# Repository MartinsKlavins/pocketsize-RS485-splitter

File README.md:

# Pocketsize RS485 splitter
Pocketsize RS485 splitter for DMX512 signal. Created for everyday use with focus on problematic device isolation, connection for far separated devices, simple "Y" type splitting.

### Technical info
* It is active, have seperate power supply for each DMX output and input.
* Galvanic and optic isolation for each DMX output and input.
* MAX485, 6N137 and 74HC14 for signal pathway.

### Notes
* AC/DC and DC/DC converters are main advantage of this splitter. Power supply is created with 4 converters. First stage – 230V AC to 12V DC, second stage – multiple 12/05V DC/DC. There are variety of them, but I don’t suggest to use 05/05 (because they didn’t gave steady 5V output, atleast not for me). Didn’t helped capacitors and LDO (for example L4941BV) for stabilization. Any way, the are small-sized and great solution!

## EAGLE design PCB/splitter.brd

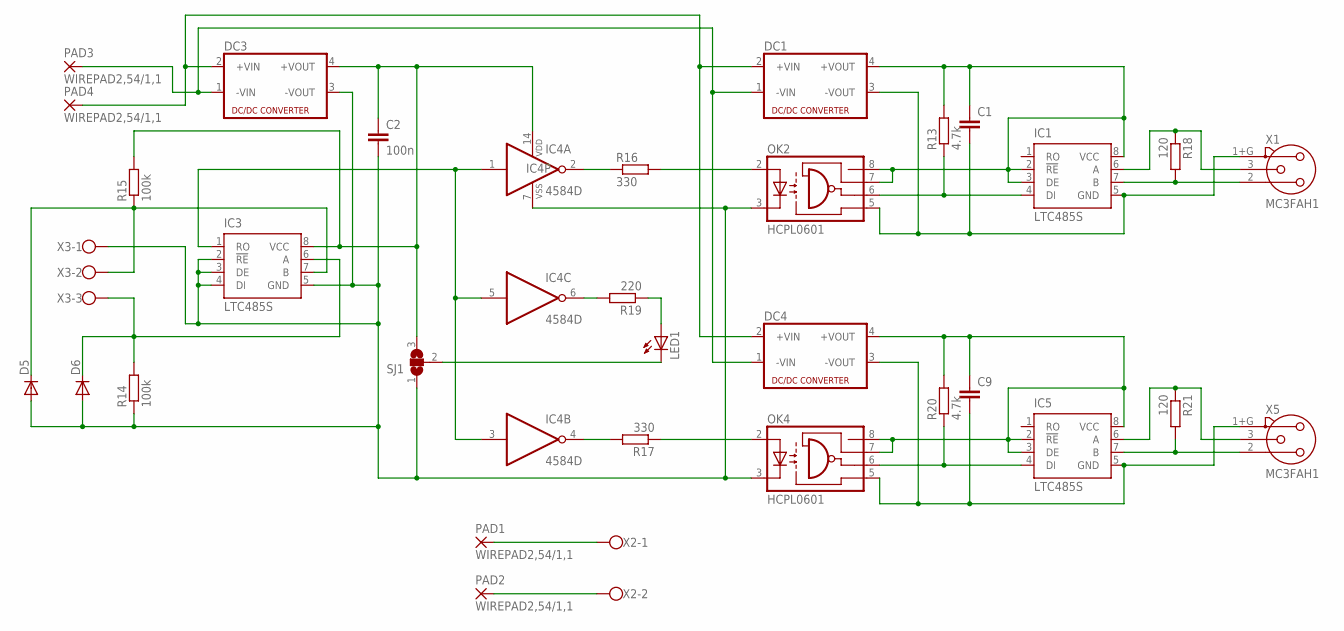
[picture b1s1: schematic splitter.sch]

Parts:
C1, C9: C-EUC1206K; C1206K
C2: 100n; C1206K
D5, D6: DIODE-SOD80C; SOD80C
DC1, DC3, DC4: NME
IC1, IC3, IC5: LTC485S; SOIC8
IC4: 4584D; SO14
LED1: LED_E; LED_1206
OK2, OK4: HCPL0601; SOIC08
PAD1, PAD2, PAD3, PAD4: WIREPAD2,54/1,1; 2,54/1,1
R13, R20: 4.7k; M1206
R14, R15: 100k; M1206
R16, R17: 330; M1206
R18, R21: 120; M1206
R19: 220; M1206
SJ1: SJ2W; SJ_2
X1, X5: MC3FAH1; NC3FAH1
X2: W237-102
X3: W237-103

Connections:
unnamed: LED1.C, SJ1.2
unnamed: IC1.6 (A), R18.1, X1.3
unnamed: IC5.7 (B), R21.2, X5.2
unnamed: IC1.4 (DI), OK2.6 (VO), R13.1
unnamed: C1.1, DC1.4 (+VOUT), IC1.2 (!RE), IC1.3 (DE), IC1.8 (VCC), OK2.7 (VE), OK2.8 (VCC), R13.2
unnamed: IC5.6 (A), R21.1, X5.3
unnamed: IC5.4 (DI), OK4.6 (VO), R20.1
unnamed: C9.2, DC4.3 (-VOUT), IC5.5 (GND), OK4.5 (GND), X5.1+G (1)
unnamed: C9.1, DC4.4 (+VOUT), IC5.2 (!RE), IC5.3 (DE), IC5.8 (VCC), OK4.7 (VE), OK4.8 (VCC), R20.2
unnamed: IC4.2 (O), R16.1
unnamed: OK2.2 (A), R16.2
unnamed: IC4.4 (O), R17.2
unnamed: OK4.2 (A), R17.1
unnamed: IC3.1 (RO), IC4.1 (I), IC4.3 (I), IC4.5 (I)
unnamed: D6.C, IC3.6 (A), R14.2, X3.3
unnamed: IC1.7 (B), R18.2, X1.2
unnamed: C2.1, DC3.4 (+VOUT), IC3.8 (VCC), IC4.14 (VDD), R15.2, SJ1.3
unnamed: C2.2, D5.A, D6.A, DC3.3 (-VOUT), IC3.2 (!RE), IC3.3 (DE), IC3.4 (DI), IC3.5 (GND), IC4.7 (VSS), OK2.3 (C), OK4.3 (C), R14.1, SJ1.1, X3.1
unnamed: D5.C, IC3.7 (B), R15.1, X3.2
unnamed: IC4.6 (O), R19.2
unnamed: DC1.1 (-VIN), DC3.1 (-VIN), DC4.1 (-VIN), PAD3.1
unnamed: DC1.2 (+VIN), DC3.2 (+VIN), DC4.2 (+VIN), PAD4.1
unnamed: PAD2.1, X2.2
unnamed: PAD1.1, X2.1
unnamed: LED1.A, R19.1
unnamed: C1.2, DC1.3 (-VOUT), IC1.5 (GND), OK2.5 (GND), X1.1+G (1)

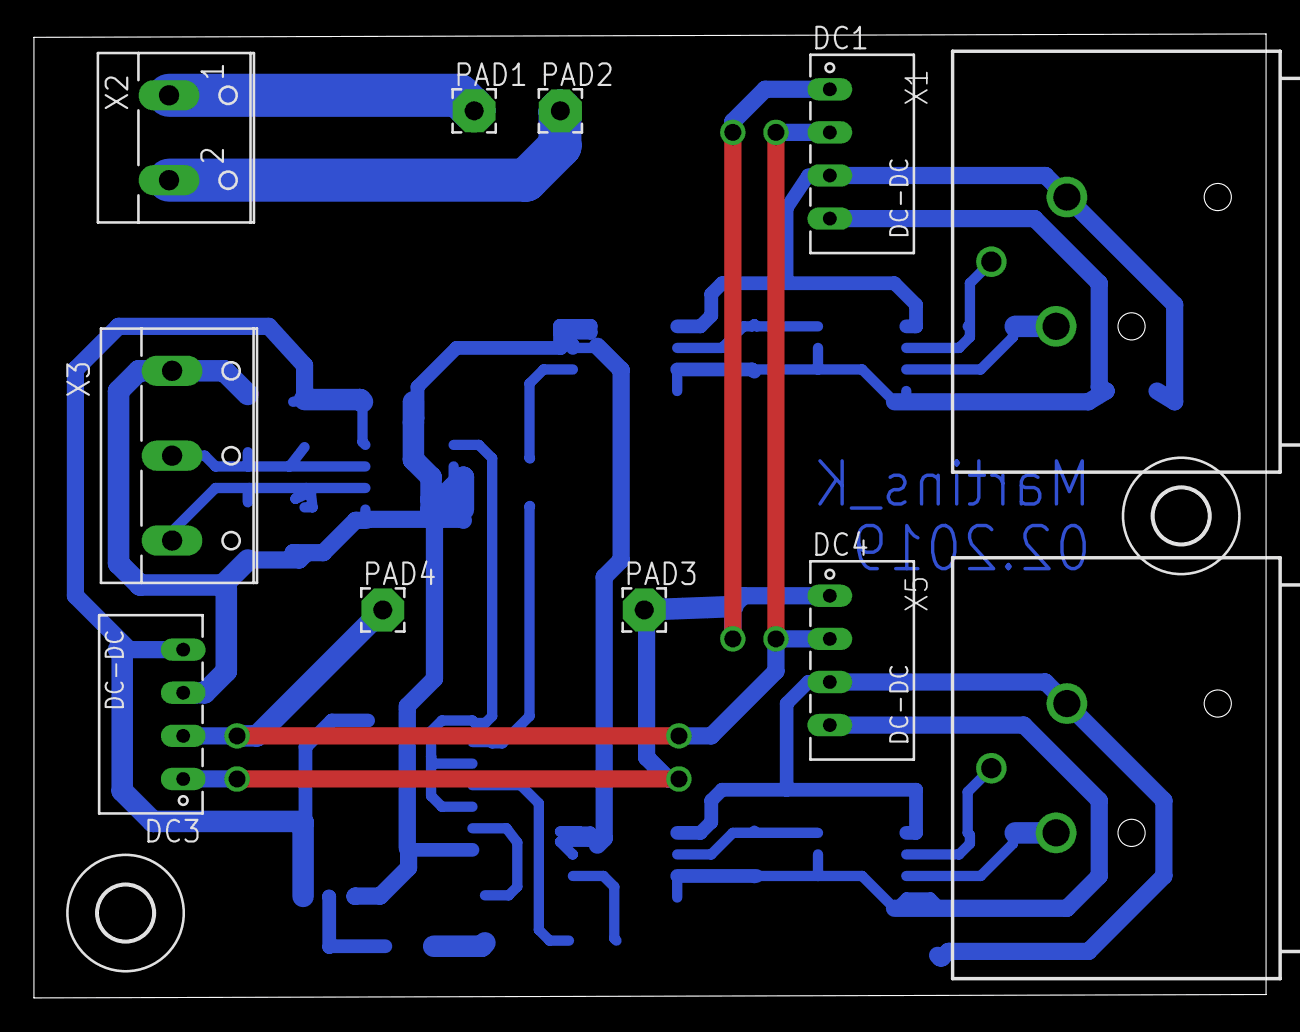
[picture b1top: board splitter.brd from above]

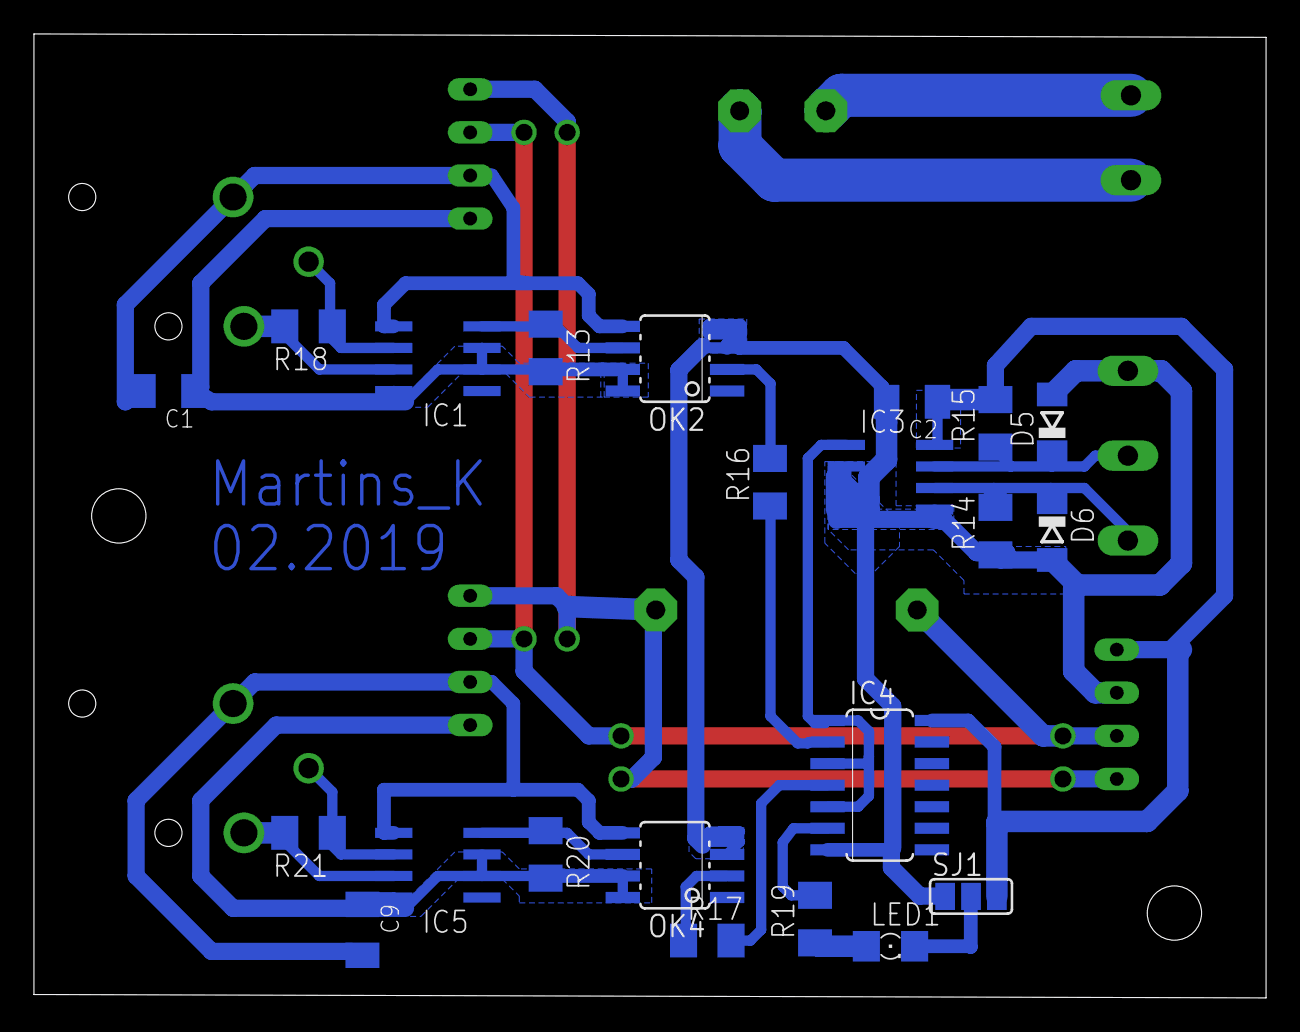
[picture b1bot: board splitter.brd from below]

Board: 2 copper layers, 72.6 x 56.8 mm, 35 parts (22 on the bottom side), 26 nets.

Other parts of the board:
U$1, U$2: 3,2
